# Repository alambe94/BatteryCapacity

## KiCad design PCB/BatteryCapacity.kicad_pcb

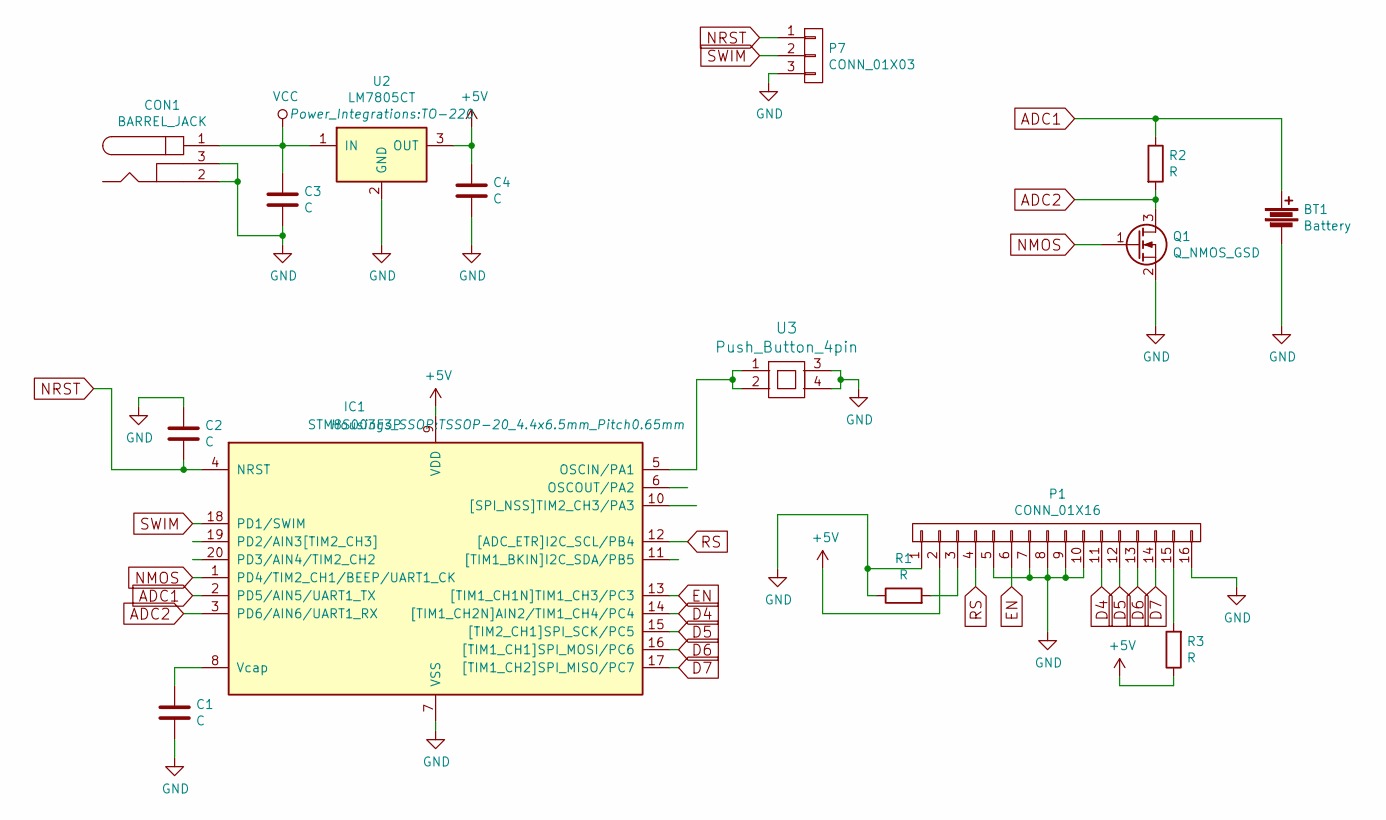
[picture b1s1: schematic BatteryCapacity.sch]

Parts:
BT1: Battery; Pin_Header_Straight_1x02
C1, C2, C3, C4: C; C_0805
CON1: BARREL_JACK; JACK_ALIM
IC1: STM8S003F3P; TSSOP-20_4.4x6.5mm_Pitch0.65mm
P1: CONN_01X16; Pin_Header_Straight_1x16
P7: CONN_01X03; Pin_Header_Straight_1x03
Q1: Q_NMOS_GSD; SOT-23
R1, R3: R; R_1206
R2: R; Resistor_Horizontal_RM30mm
U2: LM7805CT; TO-220
U3: Push_Button_4pin; SW_TH_Tactile_Omron_B3F-10xx

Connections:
+5V: C4.1, IC1.9 (VDD), P1.2, R3.1, U2.3 (OUT)
ADC1: BT1.1, IC1.2 (PD5/AIN5/UART1_TX), R2.1
ADC2: IC1.3 (PD6/AIN6/UART1_RX), Q1.3 (D), R2.2
D4: IC1.14 ([TIM1_CH2N]AIN2/TIM1_CH4/PC4), P1.11
D5: IC1.15 ([TIM2_CH1]SPI_SCK/PC5), P1.12
D6: IC1.16 ([TIM1_CH1]SPI_MOSI/PC6), P1.13
D7: IC1.17 ([TIM1_CH2]SPI_MISO/PC7), P1.14
EN: IC1.13 ([TIM1_CH1N]TIM1_CH3/PC3), P1.6
GND: BT1.2, C1.2, C2.1, C3.2, C4.2, CON1.2, CON1.3, IC1.7 (VSS), P1.1, P1.5, P1.7, P1.8, P1.9, P1.10, P1.16, P7.3, Q1.2 (S), R1.1, U2.2 (GND), U3.3, U3.4
NMOS: IC1.1 (PD4/TIM2_CH1/BEEP/UART1_CK), Q1.1 (G)
NRST: C2.2, IC1.4 (NRST), P7.1
unnamed: C1.1, IC1.8 (Vcap)
unnamed: IC1.5 (OSCIN/PA1), U3.1, U3.2
unnamed: P1.3, R1.2
unnamed: P1.15, R3.2
RS: IC1.12 ([ADC_ETR]I2C_SCL/PB4), P1.4
SWIM: IC1.18 (PD1/SWIM), P7.2
VCC: C3.1, CON1.1, U2.1 (IN)

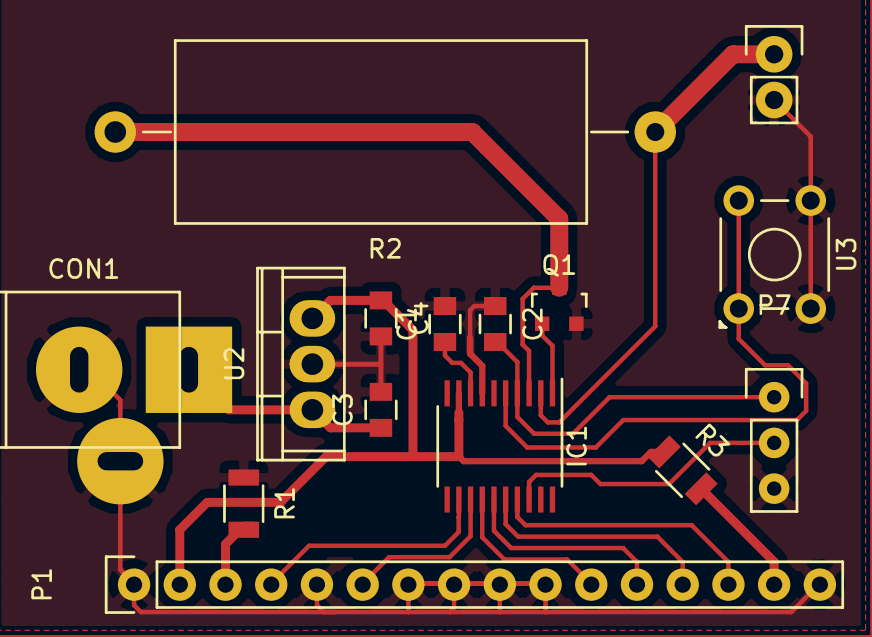
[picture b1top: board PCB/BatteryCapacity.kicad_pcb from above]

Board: 2 copper layers, 15 parts (0 on the bottom side), 18 nets.

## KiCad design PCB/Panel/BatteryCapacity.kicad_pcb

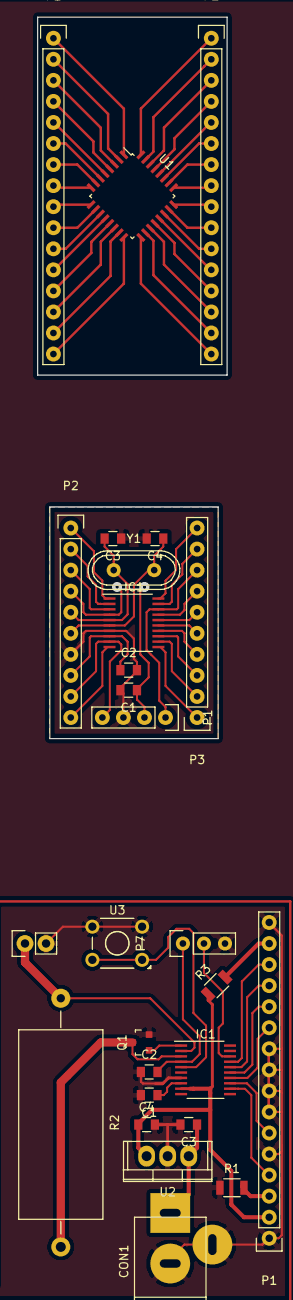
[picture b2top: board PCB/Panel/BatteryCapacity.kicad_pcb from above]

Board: 2 copper layers, 22.9 x 87.0 mm, 27 parts (0 on the bottom side), 50 nets.

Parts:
BT1: Battery; Pin_Header_Straight_1x02
C1, C1#2, C2, C2#2, C3, C3#2, C4, C4#2: C; C_0805
CON1: BARREL_JACK; JACK_ALIM
IC1, IC1#2: STM8S003F3P; TSSOP-20_4.4x6.5mm_Pitch0.65mm
P1: CONN_01X04; Pin_Header_Straight_1x04
P1#2, P1#3, P2#2: CONN_01X16; Pin_Header_Straight_1x16
P2, P3: CONN_01X10; Pin_Header_Straight_1x10
P7: CONN_01X03; Pin_Header_Straight_1x03
Q1: Q_NMOS_GSD; SOT-23
R1, R3: R; R_1206
R2: R; Resistor_Horizontal_RM30mm
U1: STM32F030K6Tx; LQFP-32_7x7mm_Pitch0.8mm
U2: LM7805CT; TO-220
U3: Push_Button_4pin; SW_TH_Tactile_Omron_B3F-10xx
Y1: CRYSTAL; Crystal_HC49-U_Vertical

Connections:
1: IC1.1, P1#3.1, P2.1, U1.1
2: IC1.2, P1#3.2, P2.2, U1.2
3: IC1.3, P1#3.3, P2.3, U1.3
4: C1.1, IC1.4, P1.2, P1#3.4, P2.4, U1.4
5: C3.2, IC1.5, P1#3.5, P2.5, U1.5, Y1.1
6: C4.1, IC1.6, P1#3.6, P2.6, U1.6, Y1.2
7: C1.2, C2.2, C3.1, C4.2, IC1.7, P1.3, P1#3.7, P2.7, U1.7
8: C2.1, IC1.8, P1#3.8, P2.8, U1.8
9: IC1.9, P1.4, P1#3.9, P2.9, U1.9
10: IC1.10, P1#3.10, P2.10, U1.10
11: IC1.11, P1#3.11, P3.1, U1.11
12: IC1.12, P1#3.12, P3.2, U1.12
13: IC1.13, P1#3.13, P3.3, U1.13
14: IC1.14, P1#3.14, P3.4, U1.14
15: IC1.15, P1#3.15, P3.5, U1.15
16: IC1.16, P1#3.16, P3.6, U1.16
17: IC1.17, P2#2.16, P3.7, U1.17
18: IC1.18, P1.1, P2#2.15, P3.8, U1.18
19: IC1.19, P2#2.14, P3.9, U1.19
20: IC1.20, P2#2.13, P3.10, U1.20
21: P2#2.12, U1.21
22: P2#2.11, U1.22
23: P2#2.10, U1.23
24: P2#2.9, U1.24
25: P2#2.8, U1.25
26: P2#2.7, U1.26
27: P2#2.6, U1.27
28: P2#2.5, U1.28
29: P2#2.4, U1.29
30: P2#2.3, U1.30
31: P2#2.2, U1.31
32: P2#2.1, U1.32
+5V: C4#2.1, IC1#2.9, P1#2.2, R3.1, U2.3
ADC1: BT1.1, IC1#2.2, R2.1
ADC2: IC1#2.3, Q1.3, R2.2
D4: IC1#2.14, P1#2.11
D5: IC1#2.15, P1#2.12
D6: IC1#2.16, P1#2.13
D7: IC1#2.17, P1#2.14
EN: IC1#2.13, P1#2.6
GND: BT1.2, C1#2.2, C2#2.1, C3#2.2, C4#2.2, CON1.2, CON1.3, IC1#2.7, P1#2.1, P1#2.5, P1#2.7, P1#2.8, P1#2.9, P1#2.10, P1#2.16, P7.3, Q1.2, R1.1, U2.2, U3.3, U3.4
NMOS: IC1#2.1, Q1.1
NRST: C2#2.2, IC1#2.4, P7.1
unnamed: C1#2.1, IC1#2.8
unnamed: IC1#2.5, U3.1, U3.2
unnamed: P1#2.3, R1.2
unnamed: P1#2.15, R3.2
RS: IC1#2.12, P1#2.4
SWIM: IC1#2.18, P7.2
VCC: C3#2.1, CON1.1, U2.1

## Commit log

2017-09-13 gitignor
